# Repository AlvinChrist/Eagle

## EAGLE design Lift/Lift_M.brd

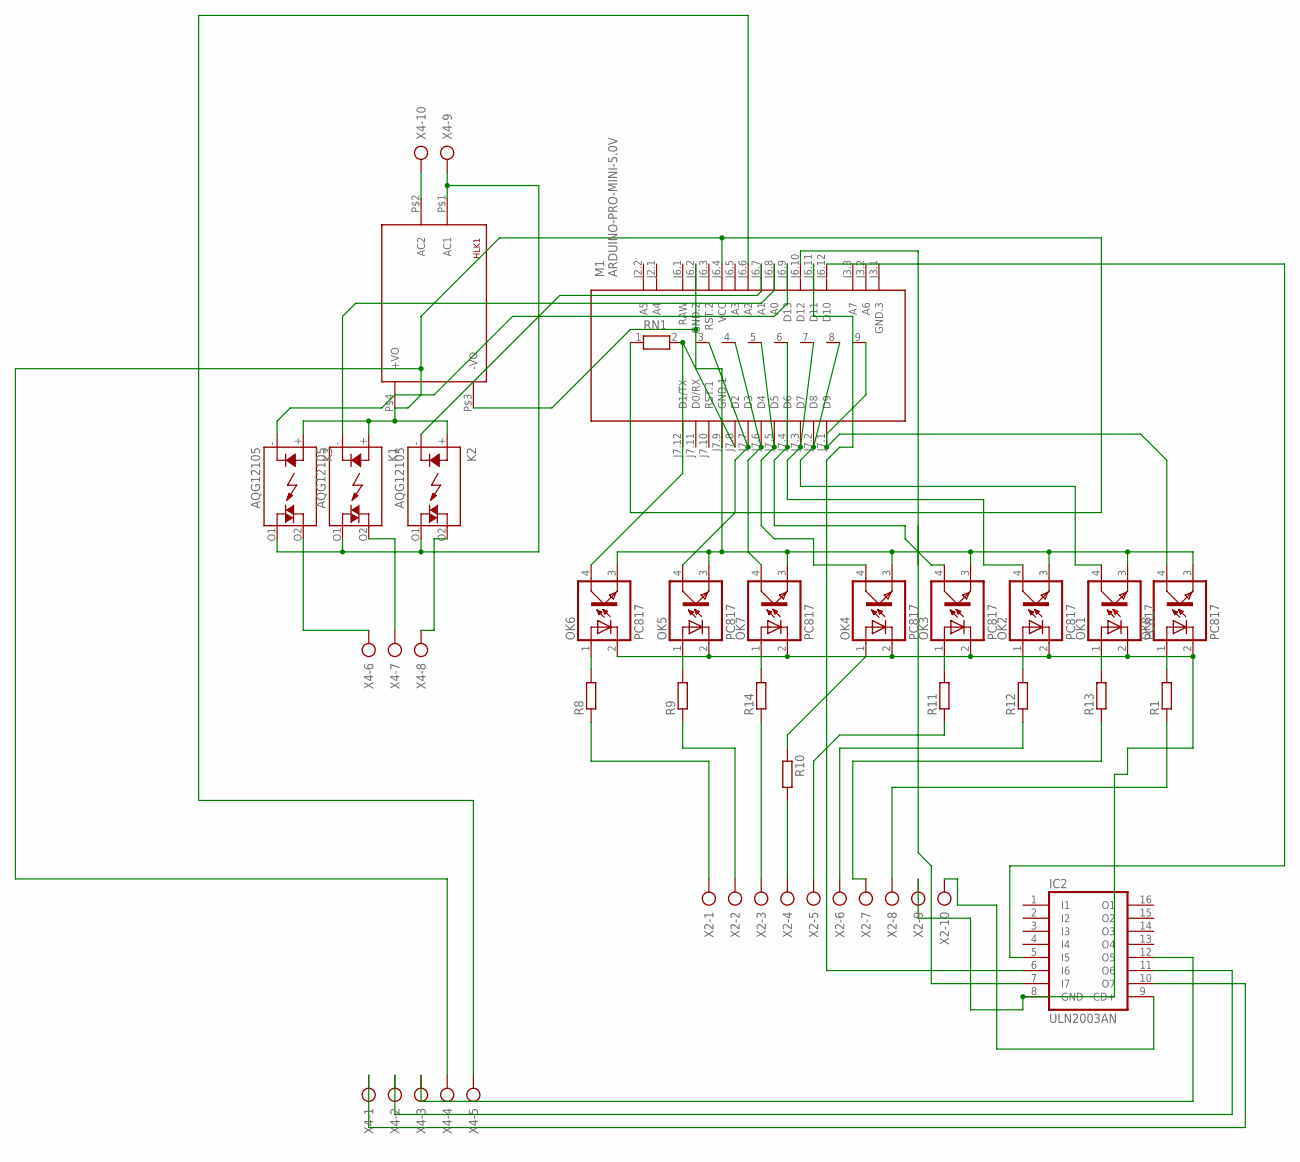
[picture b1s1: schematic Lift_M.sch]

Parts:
HLK1: HLK-PM013W; HLK-PM01
IC2: ULN2003AN; DIL16
K1, K2, K3: AQG12105; AQG
M1: ARDUINO-PRO-MINI-5.0V; ARDUINO-PRO-MINI
OK1, OK2, OK3, OK4, OK5, OK6, OK7, OK8: PC817; DIL04
R1, R8, R9, R10, R11, R12, R13, R14: R-EU_0204/7; 0204/7
RN1: RN08; RN-9
X2, X4: AK300/10

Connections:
5V: HLK1.P$4 (+VO), K1.+ (A), K2.+ (A), K3.+ (A), M1.J6.4 (VCC), RN1.1, X4.4
12V: IC2.9 (CD+), X2.10
GND1: HLK1.P$3 (-VO), M1.J6.2 (GND.2), M1.J7.9 (GND.1), OK1.3 (EMIT), OK2.3 (EMIT), OK3.3 (EMIT), OK4.3 (EMIT), OK5.3 (EMIT), OK6.3 (EMIT), OK7.3 (EMIT), OK8.3 (EMIT)
GND12V: IC2.8 (GND), OK1.2 (C), OK2.2 (C), OK3.2 (C), OK4.2 (C), OK5.2 (C), OK6.2 (C), OK7.2 (C), OK8.2 (C), X2.9
unnamed: OK2.1 (A), R12.2
unnamed: OK1.1 (A), R13.2
unnamed: OK3.1 (A), R11.2
unnamed: R10.2, X2.4
unnamed: OK7.1 (A), R14.2
unnamed: R14.1, X2.3
unnamed: R1.1, X2.8
unnamed: M1.J7.7 (D3), OK5.4 (COL), RN1.3
unnamed: M1.J7.5 (D5), OK4.4 (COL), RN1.5
unnamed: M1.J7.4 (D6), OK3.4 (COL), RN1.6
unnamed: IC2.10 (O7), X4.1
unnamed: M1.J7.6 (D4), OK7.4 (COL), RN1.4
unnamed: IC2.11 (O6), X4.2
unnamed: IC2.12 (O5), X4.3
unnamed: R8.1, X2.1
unnamed: R9.1, X2.2
unnamed: R11.1, X2.5
unnamed: M1.J7.3 (D7), OK2.4 (COL), RN1.7
unnamed: OK5.1 (A), R9.2
unnamed: R13.1, X2.7
unnamed: OK8.1 (A), R1.2
unnamed: HLK1.P$2 (AC2), X4.10
unnamed: R12.1, X2.6
unnamed: M1.J7.2 (D8), OK1.4 (COL), RN1.8
unnamed: IC2.5 (I5), M1.J6.12 (D10)
unnamed: HLK1.P$1 (AC1), K1.O1 (DS2), K2.O1 (DS2), K3.O1 (DS2), X4.9
unnamed: K3.O2 (DS1), X4.6
unnamed: K1.O2 (DS1), X4.7
unnamed: K2.O2 (DS1), X4.8
unnamed: M1.J7.1 (D9), OK8.4 (COL), RN1.9
unnamed: M1.J7.8 (D2), OK6.4 (COL), RN1.2
unnamed: OK6.1 (A), R8.2
unnamed: OK4.1 (A), R10.1
unnamed: IC2.7 (I7), M1.J6.10 (D12)
unnamed: IC2.6 (I6), M1.J6.11 (D11)
unnamed: M1.J6.6 (A2), X4.5
unnamed: K3.- (K), M1.J6.9 (D13)
unnamed: K1.- (K), M1.J6.8 (A0)
unnamed: K2.- (K), M1.J6.7 (A1)
RAW: M1.J6.1 (RAW)

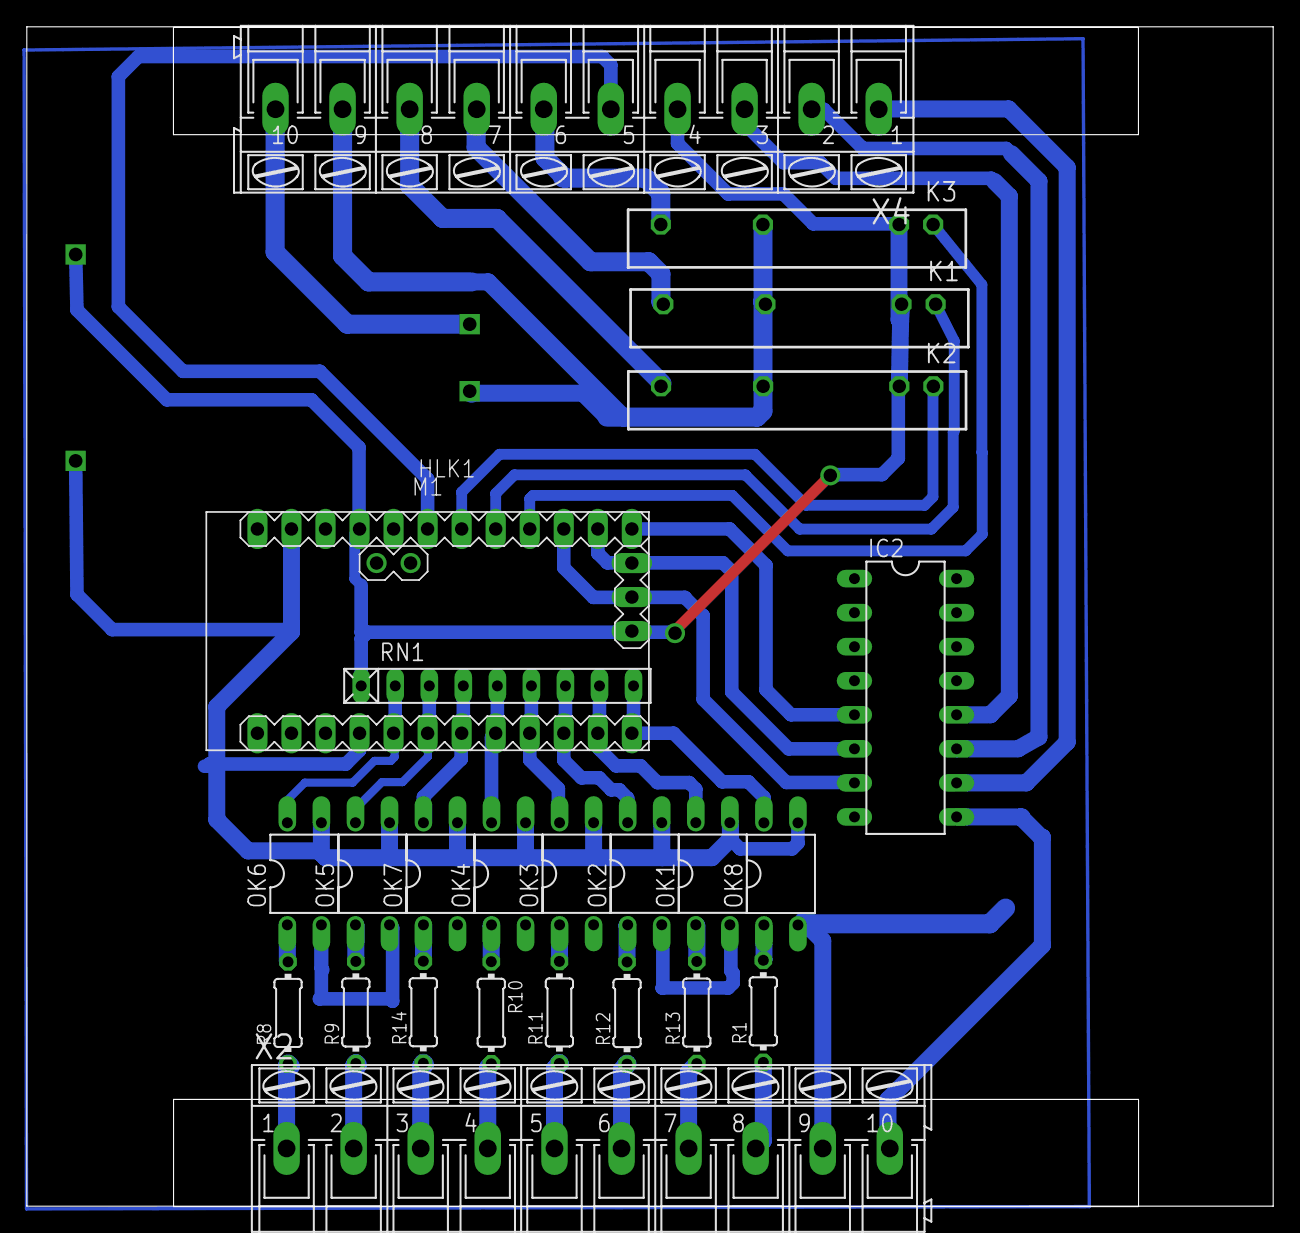
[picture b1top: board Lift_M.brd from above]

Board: 2 copper layers, 93.0 x 88.0 mm, 25 parts (0 on the bottom side), 43 nets.

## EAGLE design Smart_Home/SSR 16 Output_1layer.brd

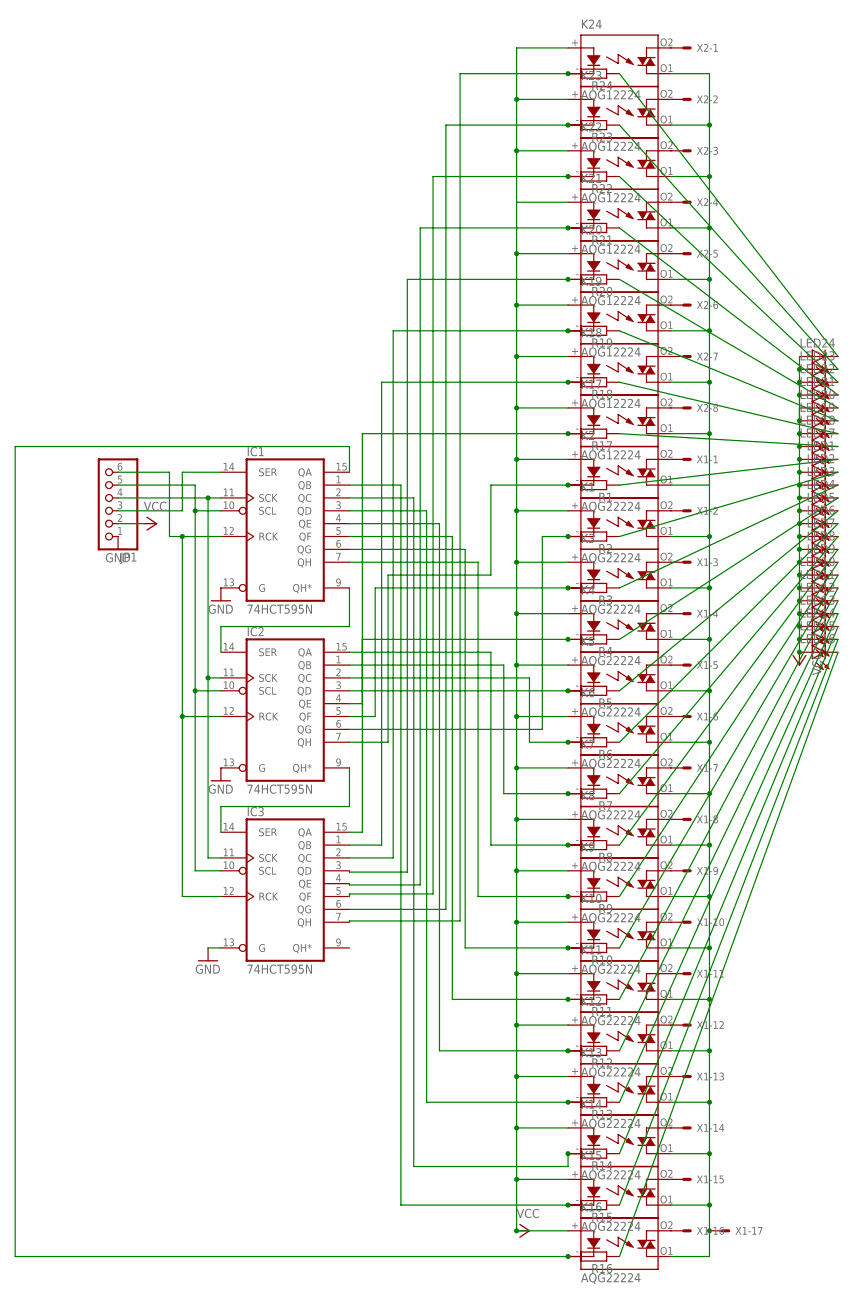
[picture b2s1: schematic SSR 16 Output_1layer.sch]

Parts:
IC1, IC2, IC3: 74HCT595N; DIL16
JP1: PINHD-1X6; 1X06
K1, K2, K3, K4, K5, K6, K7, K8, K9, K10, K11, K12, K13, K14, K15, K16: AQG22224; AQG
K17, K18, K19, K20, K21, K22, K23, K24: AQG12224; AQG
LED1, LED2, LED3, LED4, LED5, LED6, LED7, LED8, LED9, LED10, LED11, LED12, LED13, LED14, LED15, LED16, LED17, LED18, LED19, LED20, LED21, LED22, LED23, LED24: LED5MM
R1, R2, R3, R4, R5, R6, R7, R8, R9, R10, R11, R12, R13, R14, R15, R16, R17, R18, R19, R20, R21, R22, R23, R24: R0204/7; 0204/7
X1: KK-156-17
X2: KK-156-8

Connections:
GND: IC1.8 (GND), IC1.13 (G), IC2.8 (GND), IC2.13 (G), IC3.8 (GND), IC3.13 (G), JP1.1
unnamed: IC1.9 (QH*), IC2.14 (SER)
unnamed: IC1.11 (SCK), IC2.11 (SCK), IC3.11 (SCK), JP1.4
unnamed: IC1.10 (SCL), IC2.10 (SCL), IC3.10 (SCL), JP1.5
unnamed: IC1.12 (RCK), IC2.12 (RCK), IC3.12 (RCK), JP1.6
unnamed: LED1.K (C), R1.1
unnamed: IC1.15 (QA), K16.- (K), R16.2
unnamed: IC1.1 (QB), K15.- (K), R15.2
unnamed: IC1.2 (QC), K14.- (K), R14.2
unnamed: IC1.3 (QD), K13.- (K), R13.2
unnamed: IC1.4 (QE), K12.- (K), R12.2
unnamed: IC1.5 (QF), K11.- (K), R11.2
unnamed: IC1.6 (QG), K10.- (K), R10.2
unnamed: IC1.7 (QH), K9.- (K), R9.2
unnamed: IC2.15 (QA), K8.- (K), R8.2
unnamed: IC2.1 (QB), K7.- (K), R7.2
unnamed: IC2.2 (QC), K6.- (K), R6.2
unnamed: IC2.3 (QD), K5.- (K), R5.2
unnamed: IC2.4 (QE), K4.- (K), R4.2
unnamed: IC2.5 (QF), K3.- (K), R3.2
unnamed: IC2.6 (QG), K1.- (K), R2.2
unnamed: LED2.K (C), R2.1
unnamed: IC1.14 (SER), JP1.3
unnamed: K1.O1 (DS2), K2.O1 (DS2), K3.O1 (DS2), K4.O1 (DS2), K5.O1 (DS2), K6.O1 (DS2), K7.O1 (DS2), K8.O1 (DS2), K9.O1 (DS2), K10.O1 (DS2), K11.O1 (DS2), K12.O1 (DS2), K13.O1 (DS2), K14.O1 (DS2), K15.O1 (DS2), K16.O1 (DS2), K17.O1 (DS2), K18.O1 (DS2), K19.O1 (DS2), K20.O1 (DS2), K21.O1 (DS2), K22.O1 (DS2), K23.O1 (DS2), K24.O1 (DS2), X1.17
unnamed: K16.O2 (DS1), X1.16
unnamed: K15.O2 (DS1), X1.15
unnamed: K14.O2 (DS1), X1.14
unnamed: K13.O2 (DS1), X1.13
unnamed: K12.O2 (DS1), X1.12
unnamed: K11.O2 (DS1), X1.11
unnamed: K10.O2 (DS1), X1.10
unnamed: K9.O2 (DS1), X1.9
unnamed: K8.O2 (DS1), X1.8
unnamed: K7.O2 (DS1), X1.7
unnamed: K6.O2 (DS1), X1.6
unnamed: K5.O2 (DS1), X1.5
unnamed: K4.O2 (DS1), X1.4
unnamed: K3.O2 (DS1), X1.3
unnamed: K1.O2 (DS1), X1.2
unnamed: K2.O2 (DS1), X1.1
unnamed: IC2.7 (QH), K2.- (K), R1.2
unnamed: LED3.K (C), R3.1
unnamed: LED4.K (C), R4.1
unnamed: LED5.K (C), R5.1
unnamed: LED6.K (C), R6.1
unnamed: LED7.K (C), R7.1
unnamed: LED8.K (C), R8.1
unnamed: LED9.K (C), R9.1
unnamed: LED10.K (C), R10.1
unnamed: LED11.K (C), R11.1
unnamed: LED12.K (C), R12.1
unnamed: LED13.K (C), R13.1
unnamed: LED14.K (C), R14.1
unnamed: LED15.K (C), R15.1
unnamed: LED16.K (C), R16.1
unnamed: IC2.9 (QH*), IC3.14 (SER)
unnamed: IC3.15 (QA), K17.- (K), R17.2
unnamed: LED17.K (C), R17.1
unnamed: IC3.1 (QB), K18.- (K), R18.2
unnamed: LED18.K (C), R18.1
unnamed: IC3.2 (QC), K19.- (K), R19.2
unnamed: LED19.K (C), R19.1
unnamed: IC3.3 (QD), K20.- (K), R20.2
unnamed: LED20.K (C), R20.1
unnamed: IC3.4 (QE), K21.- (K), R21.2
unnamed: LED21.K (C), R21.1
unnamed: IC3.5 (QF), K22.- (K), R22.2
unnamed: LED22.K (C), R22.1
unnamed: K17.O2 (DS1), X2.8
unnamed: K18.O2 (DS1), X2.7
unnamed: K19.O2 (DS1), X2.6
unnamed: K20.O2 (DS1), X2.5
unnamed: K21.O2 (DS1), X2.4
unnamed: K22.O2 (DS1), X2.3
unnamed: K23.O2 (DS1), X2.2
unnamed: K24.O2 (DS1), X2.1
unnamed: IC3.6 (QG), K23.- (K), R23.2
unnamed: IC3.7 (QH), K24.- (K), R24.2
unnamed: LED23.K (C), R23.1
unnamed: LED24.K (C), R24.1
VCC: IC1.16 (VCC), IC2.16 (VCC), IC3.16 (VCC), JP1.2, K1.+ (A), K2.+ (A), K3.+ (A), K4.+ (A), K5.+ (A), K6.+ (A), K7.+ (A), K8.+ (A), K9.+ (A), K10.+ (A), K11.+ (A), K12.+ (A), K13.+ (A), K14.+ (A), K15.+ (A), K16.+ (A), K17.+ (A), K18.+ (A), K19.+ (A), K20.+ (A), K21.+ (A), K22.+ (A), K23.+ (A), K24.+ (A), LED1.A, LED2.A, LED3.A, LED4.A, LED5.A, LED6.A, LED7.A, LED8.A, LED9.A, LED10.A, LED11.A, LED12.A, LED13.A, LED14.A, LED15.A, LED16.A, LED17.A, LED18.A, LED19.A, LED20.A, LED21.A, LED22.A, LED23.A, LED24.A

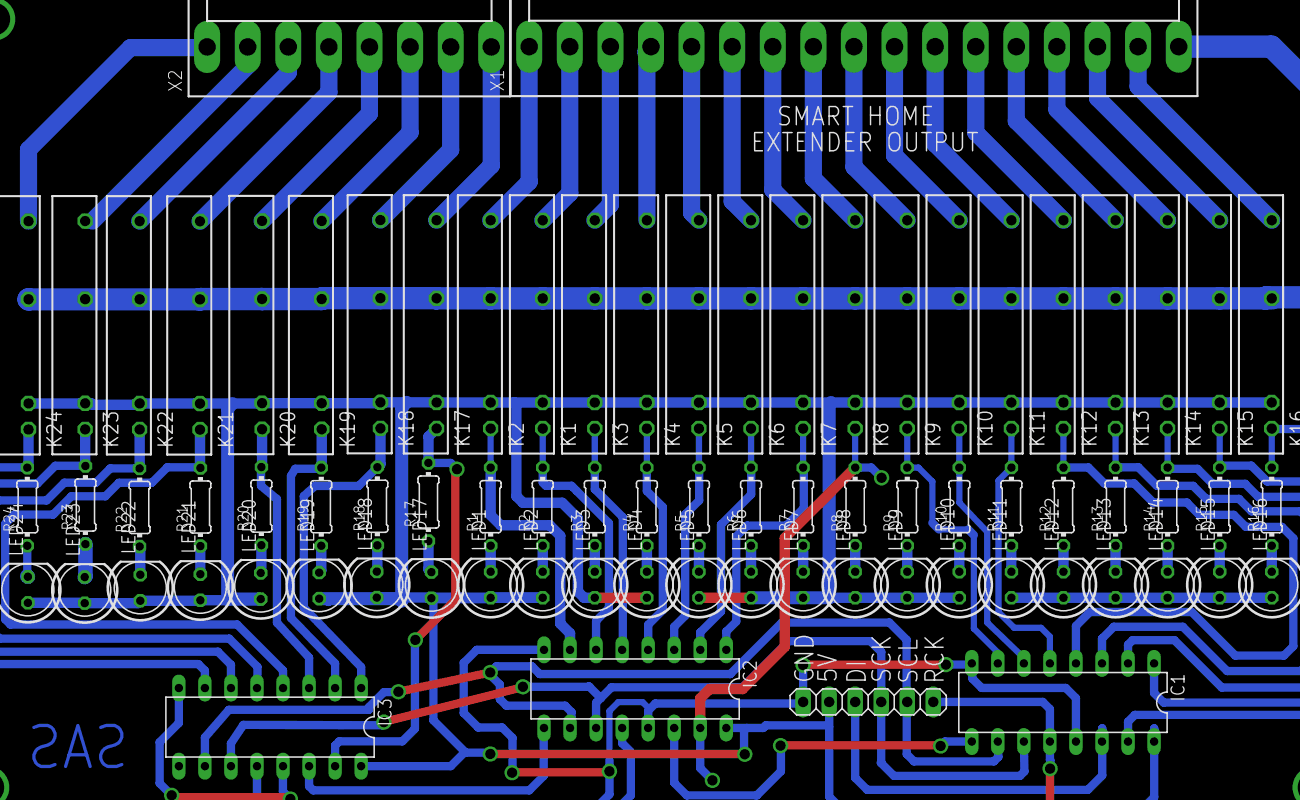
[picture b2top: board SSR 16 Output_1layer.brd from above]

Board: 2 copper layers, 78 parts (0 on the bottom side), 81 nets.

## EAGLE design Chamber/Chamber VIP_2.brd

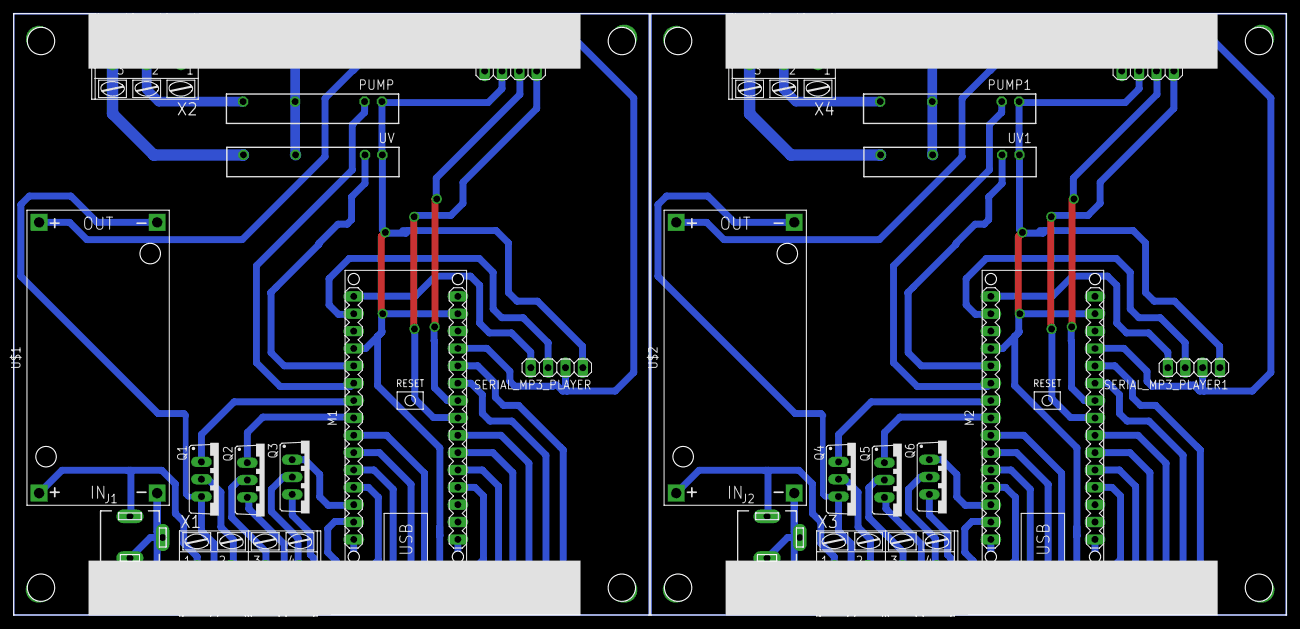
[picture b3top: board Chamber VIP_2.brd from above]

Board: 2 copper layers, 186.2 x 88.0 mm, 28 parts (0 on the bottom side), 62 nets.

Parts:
E$1, E$6: 1X12
E$2, E$3: 1X02
E$4, E$5: 1X04
J1, J2: DCJ0202
M1, M2: ARDUINO-NANO-3.0#ISP; ARDUINO-NANO-3.0
PUMP, PUMP1: AQG12105; AQG
Q1, Q2, Q3, Q4, Q5, Q6: IRF540; TO220BV
SERIAL_MP3_PLAYER, SERIAL_MP3_PLAYER1: 1X04
U$1, U$2: DC-DC-STEP-DOWN-LM2596
UV, UV1: AQG12105; AQG
X1, X3: AK300/4
X2, X4: AK300/3

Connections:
+5V: E$4.1, M1.J2.4, SERIAL_MP3_PLAYER.2, U$1.OUT+
+5V1: E$5.1, M2.J2.4, SERIAL_MP3_PLAYER1.2, U$2.OUT+
GND: E$1.7, E$4.2, J1.2, J1.3, M1.J1.4, M1.J2.2, PUMP.-, Q1.S, Q2.S, Q3.S, SERIAL_MP3_PLAYER.1, U$1.IN-, U$1.OUT-, UV.-
GND1: E$5.2, E$6.7, J2.2, J2.3, M2.J1.4, M2.J2.2, PUMP1.-, Q4.S, Q5.S, Q6.S, SERIAL_MP3_PLAYER1.1, U$2.IN-, U$2.OUT-, UV1.-
unnamed: Q3.D, X1.4
unnamed: J1.1, U$1.IN+, X1.1
unnamed: Q1.D, X1.2
unnamed: Q2.D, X1.3
unnamed: J2.1, U$2.IN+, X3.1
unnamed: PUMP.O2, X2.2
unnamed: PUMP.O1, UV.O1, X2.1
unnamed: Q4.D, X3.2
unnamed: PUMP1.O2, X4.2
unnamed: PUMP1.O1, UV1.O1, X4.1
unnamed: M2.J1.5, UV1.+
unnamed: Q6.D, X3.4
unnamed: M1.J1.5, UV.+
unnamed: Q5.D, X3.3
unnamed: M2.J1.6, PUMP1.+
unnamed: M1.J1.6, PUMP.+
unnamed: E$1.2, M1.J1.15
unnamed: UV.O2, X2.3
unnamed: E$6.2, M2.J1.15
unnamed: UV1.O2, X4.3
S$1: E$4.3, M1.J2.7
S$4: M1.J1.2, SERIAL_MP3_PLAYER.3
S$5: M1.J1.1, SERIAL_MP3_PLAYER.4
S$6: E$1.6, M1.J1.9
S$7: M1.J1.7, Q1.G
S$8: E$1.4, M1.J1.11
S$9: E$1.3, M1.J1.12
S$10: M1.J1.13, Q3.G
S$11: E$1.1, M1.J1.14
S$12: E$2.2, M1.J2.5
S$13: E$2.1, M1.J2.6
S$14: E$1.12, M1.J2.9
S$15: E$1.11, M1.J2.10
S$16: E$1.10, M1.J2.11
S$17: E$1.9, M1.J2.12
S$18: E$1.8, M1.J2.15
S$19: M1.J1.8, Q2.G
S$20: E$4.4, M1.J2.8
S$21: E$1.5, M1.J1.10
S$23: E$6.5, M2.J1.10
S$24: E$6.4, M2.J1.11
S$25: E$6.6, M2.J1.9
S$26: M2.J1.2, SERIAL_MP3_PLAYER1.3
S$27: M2.J1.7, Q4.G
S$29: M2.J1.1, SERIAL_MP3_PLAYER1.4
S$30: E$6.3, M2.J1.12
S$31: M2.J1.13, Q6.G
S$32: E$6.1, M2.J1.14
S$33: E$3.2, M2.J2.5
S$34: E$3.1, M2.J2.6
S$35: E$6.12, M2.J2.9
S$36: E$6.11, M2.J2.10
S$37: E$6.10, M2.J2.11
S$38: E$6.9, M2.J2.12
S$39: E$6.8, M2.J2.15
S$40: E$5.3, M2.J2.7
S$41: E$5.4, M2.J2.8
S$42: M2.J1.8, Q5.G

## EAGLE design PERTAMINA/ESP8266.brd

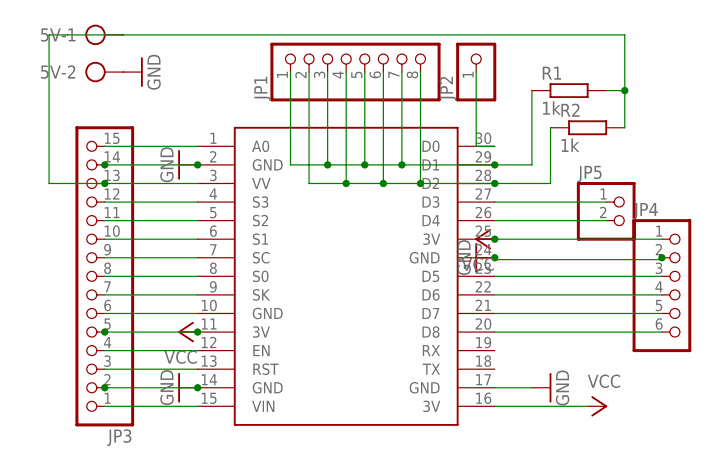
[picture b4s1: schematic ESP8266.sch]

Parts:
5V: AK300/2
JP1: PINHD-1X8; 1X08
JP2: PINHD-1X1; 1X01
JP3: PINHD-1X15; 1X15
JP4: PINHD-1X6; 1X06
JP5: PINHD-1X2; 1X02
R1, R2: 1k; 0204/7
U$1: NODEMCU

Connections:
GND: 5V.2, JP3.2, JP3.14, JP4.2, U$1.2 (GND), U$1.14 (GND), U$1.17 (GND), U$1.24 (GND)
unnamed: JP3.1, U$1.15 (VIN)
unnamed: JP3.3, U$1.13 (RST)
unnamed: JP3.4, U$1.12 (EN)
unnamed: JP3.6, U$1.10 (GND)
unnamed: JP3.7, U$1.9 (SK)
unnamed: JP3.8, U$1.8 (S0)
unnamed: JP3.9, U$1.7 (SC)
unnamed: JP3.10, U$1.6 (S1)
unnamed: JP3.11, U$1.5 (S2)
unnamed: JP3.12, U$1.4 (S3)
unnamed: 5V.1, JP3.13, R1.2, R2.2, U$1.3 (VV)
unnamed: JP3.15, U$1.1 (A0)
unnamed: JP4.3, U$1.23 (D5)
unnamed: JP4.4, U$1.22 (D6)
unnamed: JP4.5, U$1.21 (D7)
unnamed: JP4.6, U$1.20 (D8)
unnamed: JP5.1, U$1.27 (D3)
unnamed: JP5.2, U$1.26 (D4)
SCL: JP1.1, JP1.3, JP1.5, JP1.7, R1.1, U$1.29 (D1)
SDA: JP1.2, JP1.4, JP1.6, JP1.8, R2.1, U$1.28 (D2)
VCC: JP3.5, JP4.1, U$1.11 (3V), U$1.16 (3V), U$1.25 (3V)

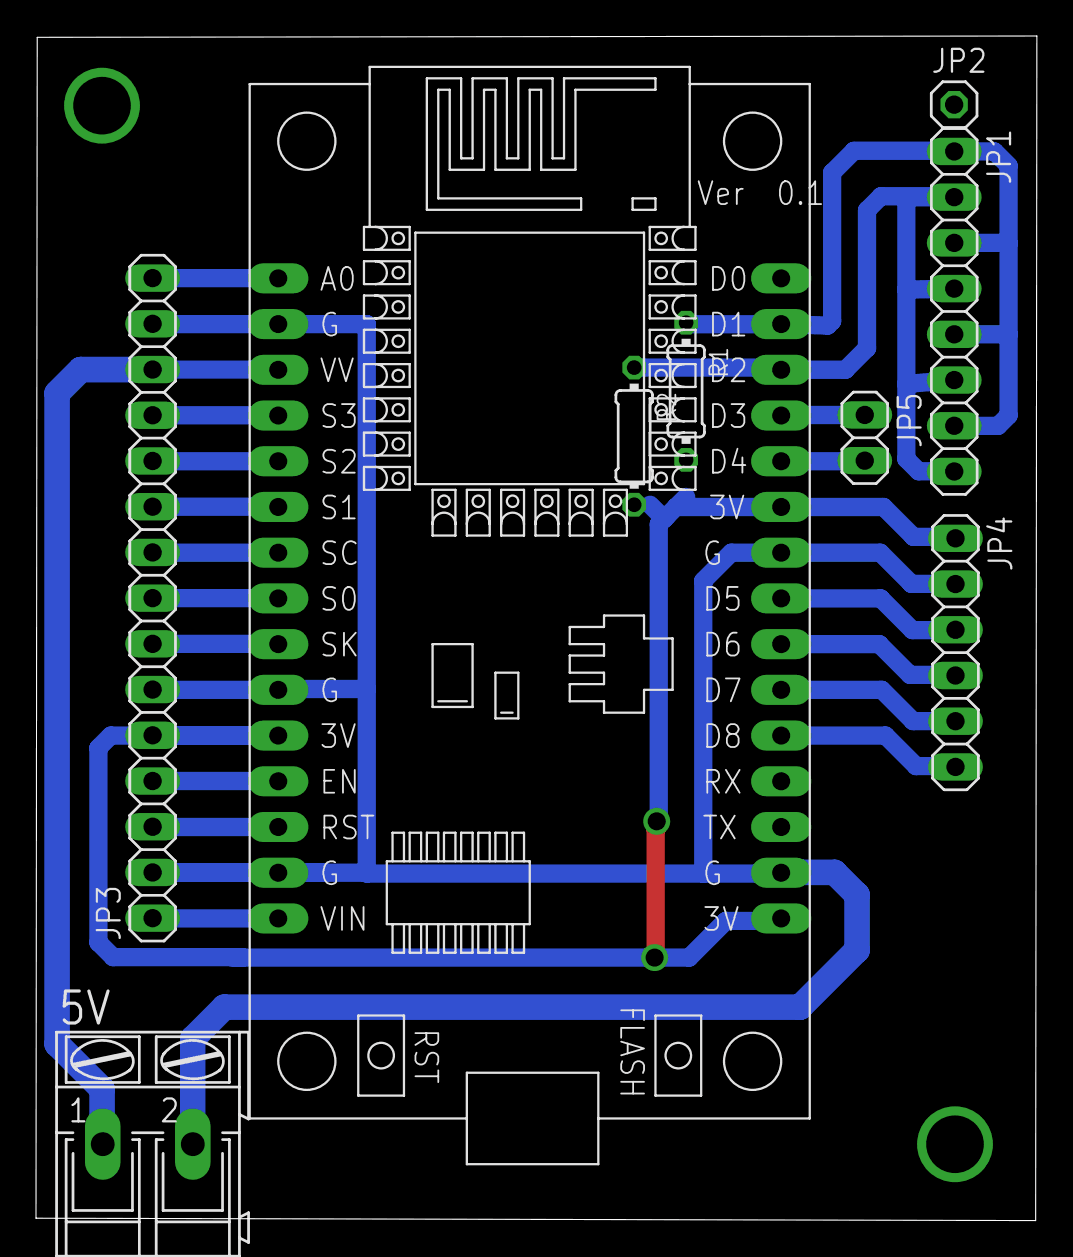
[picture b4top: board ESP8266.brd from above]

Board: 2 copper layers, 55.6 x 65.8 mm, 9 parts (0 on the bottom side), 22 nets.

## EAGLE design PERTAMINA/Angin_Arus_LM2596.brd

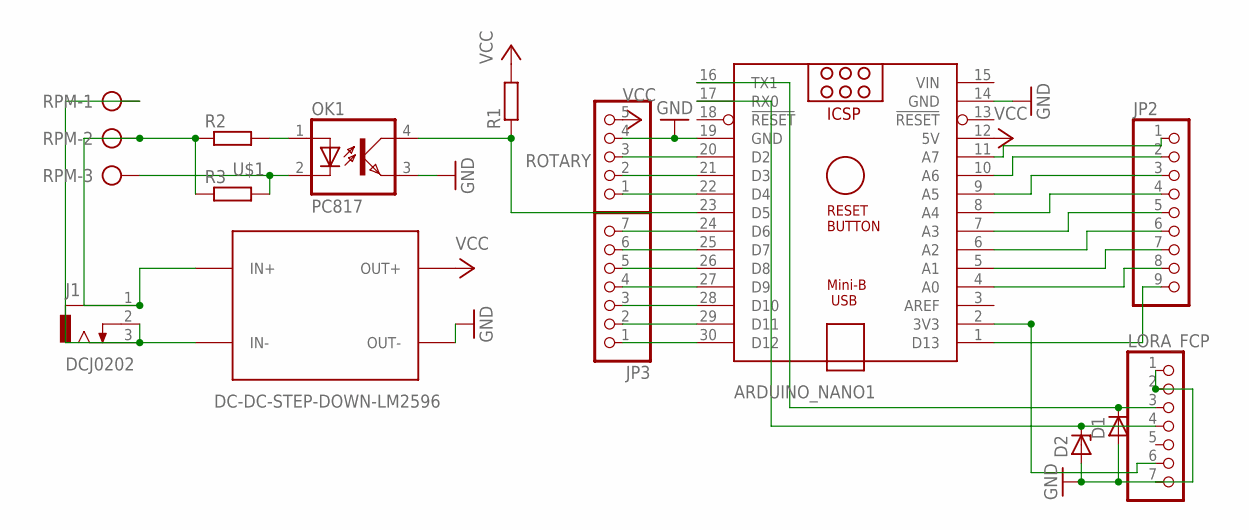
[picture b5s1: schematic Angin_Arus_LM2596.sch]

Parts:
ARDUINO_NANO1: ARDUINO_NANO
D1, D2: ZENER-DIODEDO35Z10; DO35Z10
J1: DCJ0202
JP2: PINHD-1X9; 1X09
JP3: PINHD-1X7; 1X07
LORA_FCP: PINHD-1X7; 1X07
OK1: PC817; DIL04
R1, R2, R3: R-EU_0204/7; 0204/7
ROTARY: PINHD-1X5; 1X05
RPM: AK300/3
U$1: DC-DC-STEP-DOWN-LM2596

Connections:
3.3V: ARDUINO_NANO1.2 (3V3), LORA_FCP.6
12V: J1.1, R2.1, R3.1, RPM.2, U$1.IN+
GND: ARDUINO_NANO1.14 (GND), ARDUINO_NANO1.19 (GND), D1.A, D2.A, LORA_FCP.1, LORA_FCP.2, LORA_FCP.7, OK1.3 (EMIT), ROTARY.4, U$1.OUT-
GND12V: J1.2, J1.3, RPM.1, U$1.IN-
unnamed: ARDUINO_NANO1.23 (D5), OK1.4 (COL), R1.1
unnamed: OK1.1 (A), R2.2
unnamed: ARDUINO_NANO1.20 (D2), ROTARY.3
unnamed: ARDUINO_NANO1.21 (D3), ROTARY.2
unnamed: ARDUINO_NANO1.22 (D4), ROTARY.1
unnamed: ARDUINO_NANO1.8 (A4), JP2.4
unnamed: ARDUINO_NANO1.1 (D13), JP2.9
unnamed: ARDUINO_NANO1.4 (A0), JP2.8
unnamed: ARDUINO_NANO1.5 (A1), JP2.7
unnamed: ARDUINO_NANO1.6 (A2), JP2.6
unnamed: ARDUINO_NANO1.7 (A3), JP2.5
unnamed: ARDUINO_NANO1.9 (A5), JP2.3
unnamed: ARDUINO_NANO1.10 (A6), JP2.2
unnamed: ARDUINO_NANO1.11 (A7), JP2.1
unnamed: ARDUINO_NANO1.30 (D12), JP3.1
unnamed: ARDUINO_NANO1.29 (D11), JP3.2
unnamed: ARDUINO_NANO1.28 (D10), JP3.3
unnamed: ARDUINO_NANO1.27 (D9), JP3.4
unnamed: ARDUINO_NANO1.26 (D8), JP3.5
unnamed: ARDUINO_NANO1.25 (D7), JP3.6
unnamed: ARDUINO_NANO1.24 (D6), JP3.7
RX: ARDUINO_NANO1.16 (TX1), D1.C, LORA_FCP.3
SIGNAL: OK1.2 (C), R3.2, RPM.3
TX: ARDUINO_NANO1.17 (RX0), D2.C, LORA_FCP.4
VCC: ARDUINO_NANO1.12 (5V), R1.2, ROTARY.5, U$1.OUT+
VIN: ARDUINO_NANO1.15 (VIN)

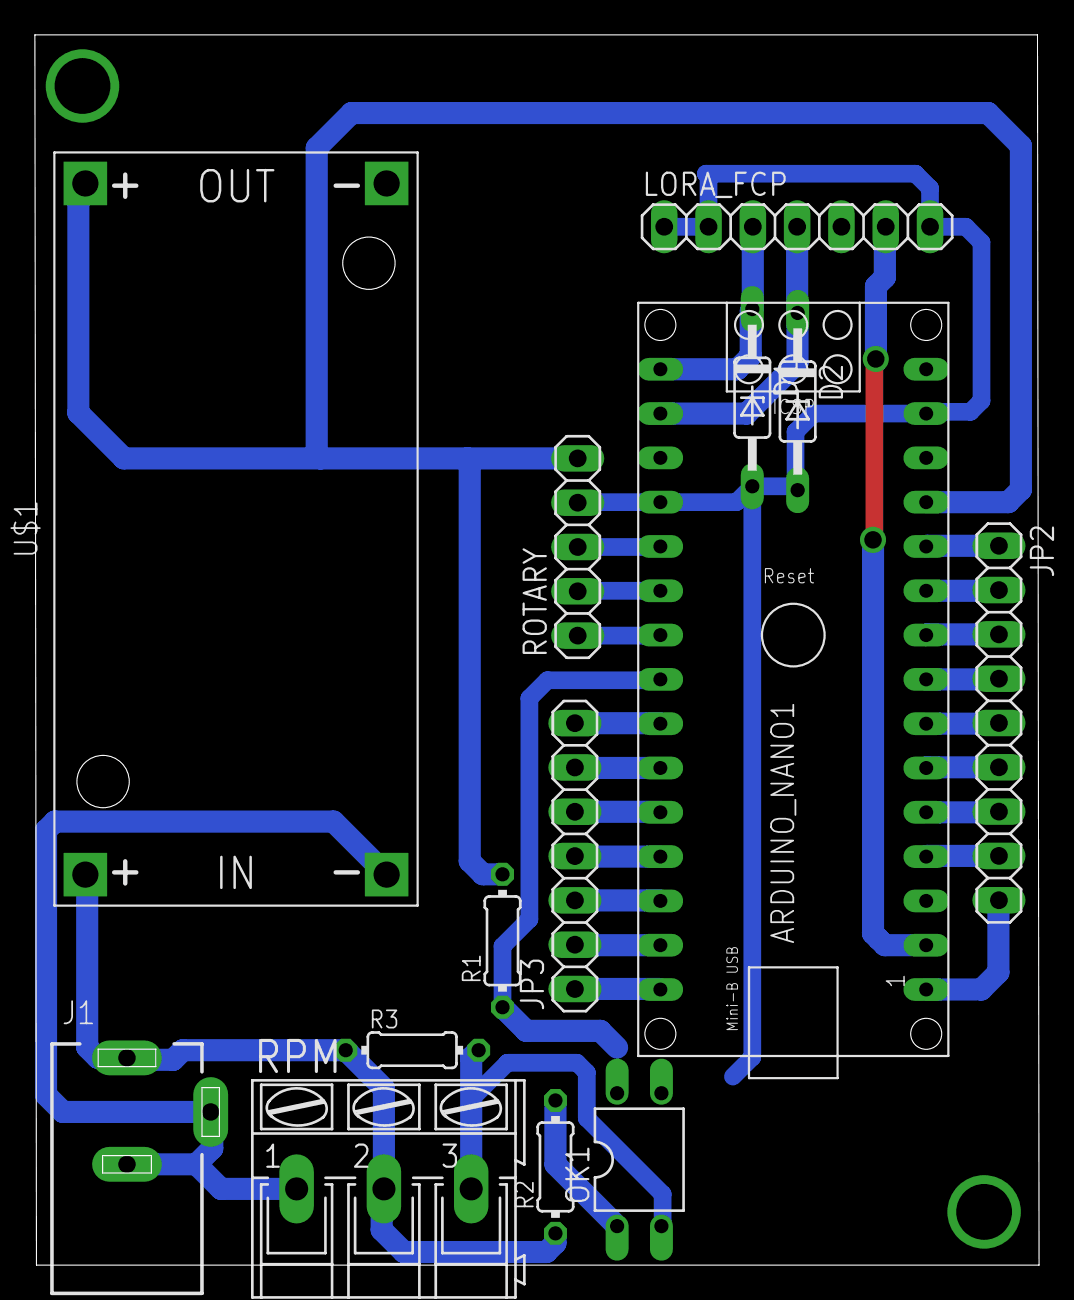
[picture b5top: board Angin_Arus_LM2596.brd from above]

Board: 2 copper layers, 57.6 x 70.5 mm, 14 parts (0 on the bottom side), 29 nets.

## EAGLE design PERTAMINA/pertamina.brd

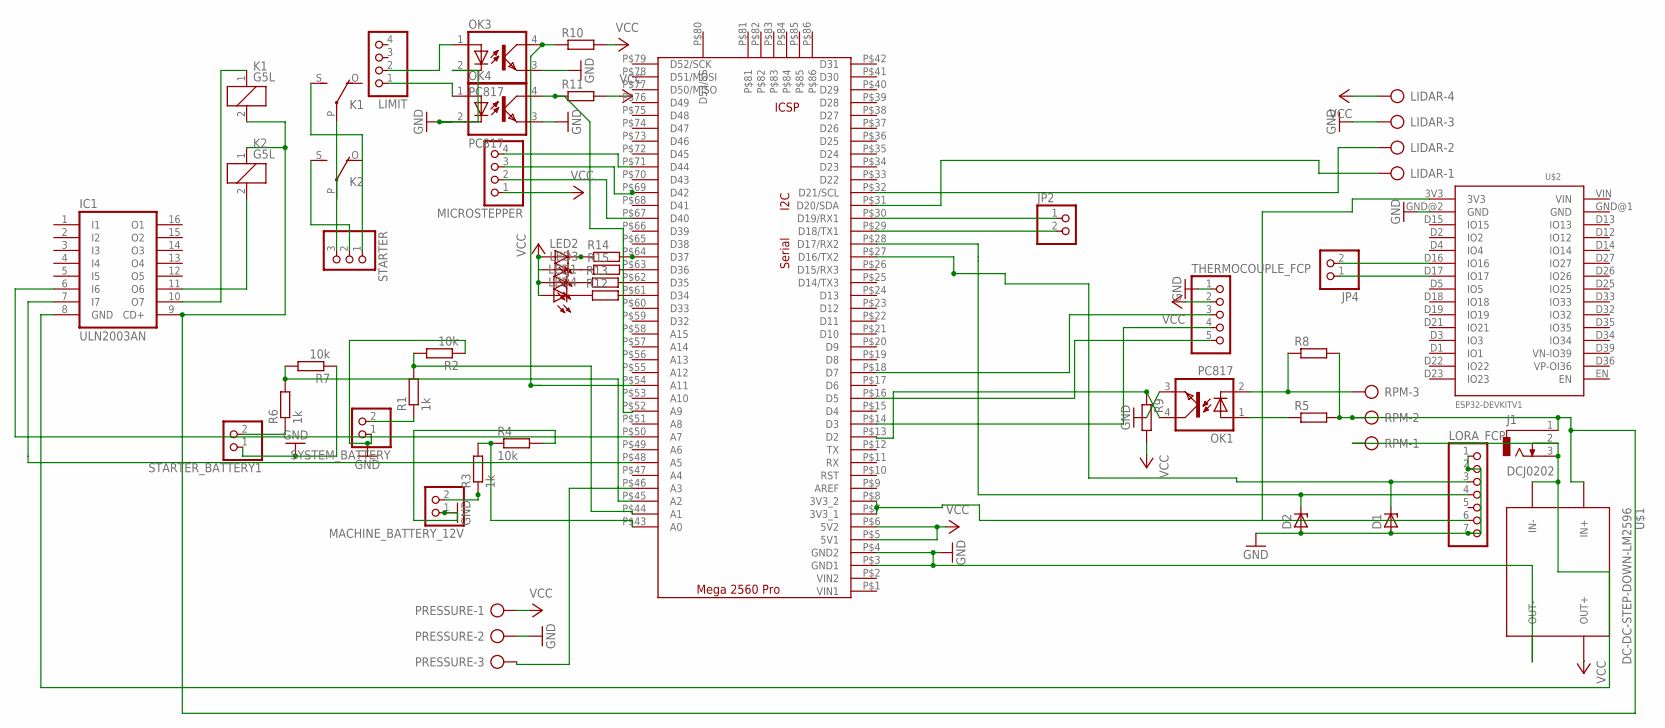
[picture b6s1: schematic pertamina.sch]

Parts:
D1, D2: ZENER-DIODEDO35Z10; DO35Z10
IC1: ULN2003AN; DIL16
J1: DCJ0202
JP2, JP4: PINHD-1X2; 1X02
K1, K2: G5L; G5LE
LED1, LED2, LED3, LED4: LED5MM
LIDAR: AK300/4
LIMIT: PINHD-1X4; 1X04
LORA_FCP: PINHD-1X7; 1X07
MACHINE_BATTERY_12V: PINHD-1X2; 1X02
MICROSTEPPER: PINHD-1X4; 1X04
OK1, OK3, OK4: PC817; DIL04
PRESSURE: AK300/3
R1, R3, R6: 1k; 0204/7
R2, R4, R7: 10k; 0204/7
R5, R8, R9, R10, R11, R12, R13, R14, R15: R-EU_0204/7; 0204/7
RPM: AK300/3
STARTER: PINHD-1X3; 1X03
STARTER_BATTERY1: PINHD-1X2; 1X02
SYSTEM_BATTERY: PINHD-1X2; 1X02
THERMOCOUPLE_FCP: PINHD-1X5; 1X05
U$1: DC-DC-STEP-DOWN-LM2596
U$2: ESP32DEVKITV1; ESP32-DEVKITV1
U$3: MEGAPROMINI

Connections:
3.3V: LORA_FCP.6, U$2.3V3, U$3.P$7 (3V3_1), U$3.P$8 (3V3_2)
5V: R1.2, R2.2, U$3.P$44 (A1)
5V1: R6.2, R7.2, U$3.P$45 (A2)
5V_ARDU: LED1.A, LED2.A, LED3.A, LED4.A, LIDAR.4, MICROSTEPPER.1, PRESSURE.1, R9.2, R10.2, R11.2, THERMOCOUPLE_FCP.2, U$1.OUT+, U$3.P$5 (5V1), U$3.P$6 (5V2)
GND: D1.A, D2.A, LIDAR.3, LORA_FCP.1, LORA_FCP.2, LORA_FCP.7, MACHINE_BATTERY_12V.1, OK1.3 (EMIT), OK3.2 (C), OK3.3 (EMIT), OK4.2 (C), OK4.3 (EMIT), PRESSURE.2, R2.1, R4.2, R7.1, STARTER_BATTERY1.1, SYSTEM_BATTERY.1, THERMOCOUPLE_FCP.1, U$1.OUT-, U$2.GND@2 (GND), U$3.P$3 (GND1), U$3.P$4 (GND2)
unnamed: JP2.1, U$3.P$30 (D19/RX1)
unnamed: JP2.2, U$3.P$29 (D18/TX1)
unnamed: R3.2, R4.1, U$3.P$43 (A0)
unnamed: IC1.10 (O7), K1.1
unnamed: THERMOCOUPLE_FCP.5, U$3.P$16 (D5)
unnamed: THERMOCOUPLE_FCP.4, U$3.P$14 (D3)
unnamed: THERMOCOUPLE_FCP.3, U$3.P$18 (D7)
unnamed: D2.C, LORA_FCP.4, U$3.P$28 (D17/RX2)
unnamed: R1.1, SYSTEM_BATTERY.2
unnamed: IC1.9 (CD+), J1.1, K1.2, K2.1, R5.2, R8.2, RPM.2, U$1.IN+
unnamed: D1.C, LORA_FCP.3, U$3.P$27 (D16/TX2)
unnamed: MACHINE_BATTERY_12V.2, R3.1
unnamed: IC1.8 (GND), J1.2, J1.3, RPM.1, U$1.IN-
unnamed: OK1.1 (A), R5.1
unnamed: OK1.4 (COL), R9.1, U$3.P$13 (D2)
unnamed: OK1.2 (C), R8.1, RPM.3
unnamed: JP4.1, U$2.D17 (IO17)
unnamed: JP4.2, U$2.D16 (IO16)
unnamed: IC1.7 (I7), U$3.P$48 (A5)
unnamed: R6.1, STARTER_BATTERY1.2
unnamed: R12.2, U$3.P$61 (D34)
unnamed: LED4.K (C), R12.1
unnamed: R14.2, U$3.P$64 (D37)
unnamed: IC1.6 (I6), U$3.P$50 (A7)
unnamed: MICROSTEPPER.4, U$3.P$71 (D44)
unnamed: MICROSTEPPER.2, U$3.P$67 (D40)
unnamed: MICROSTEPPER.3, U$3.P$69 (D42)
unnamed: PRESSURE.3, U$3.P$46 (A3)
unnamed: LED2.K (C), R14.1
unnamed: IC1.11 (O6), K2.2
unnamed: R13.2, U$3.P$62 (D35)
unnamed: LED1.K (C), R13.1
unnamed: R15.2, U$3.P$63 (D36)
unnamed: LED3.K (C), R15.1
unnamed: LIMIT.1, OK4.1 (A)
unnamed: LIMIT.2, OK3.1 (A)
unnamed: OK4.4 (COL), R11.1, U$3.P$52 (A9)
unnamed: K1.P, K2.P, STARTER.3
unnamed: K2.S, STARTER.2
unnamed: K1.S, STARTER.1
unnamed: OK3.4 (COL), R10.1, U$3.P$54 (A11)
SCL: LIDAR.2, U$3.P$32 (D21/SCL)
SDA: LIDAR.1, U$3.P$31 (D20/SDA)

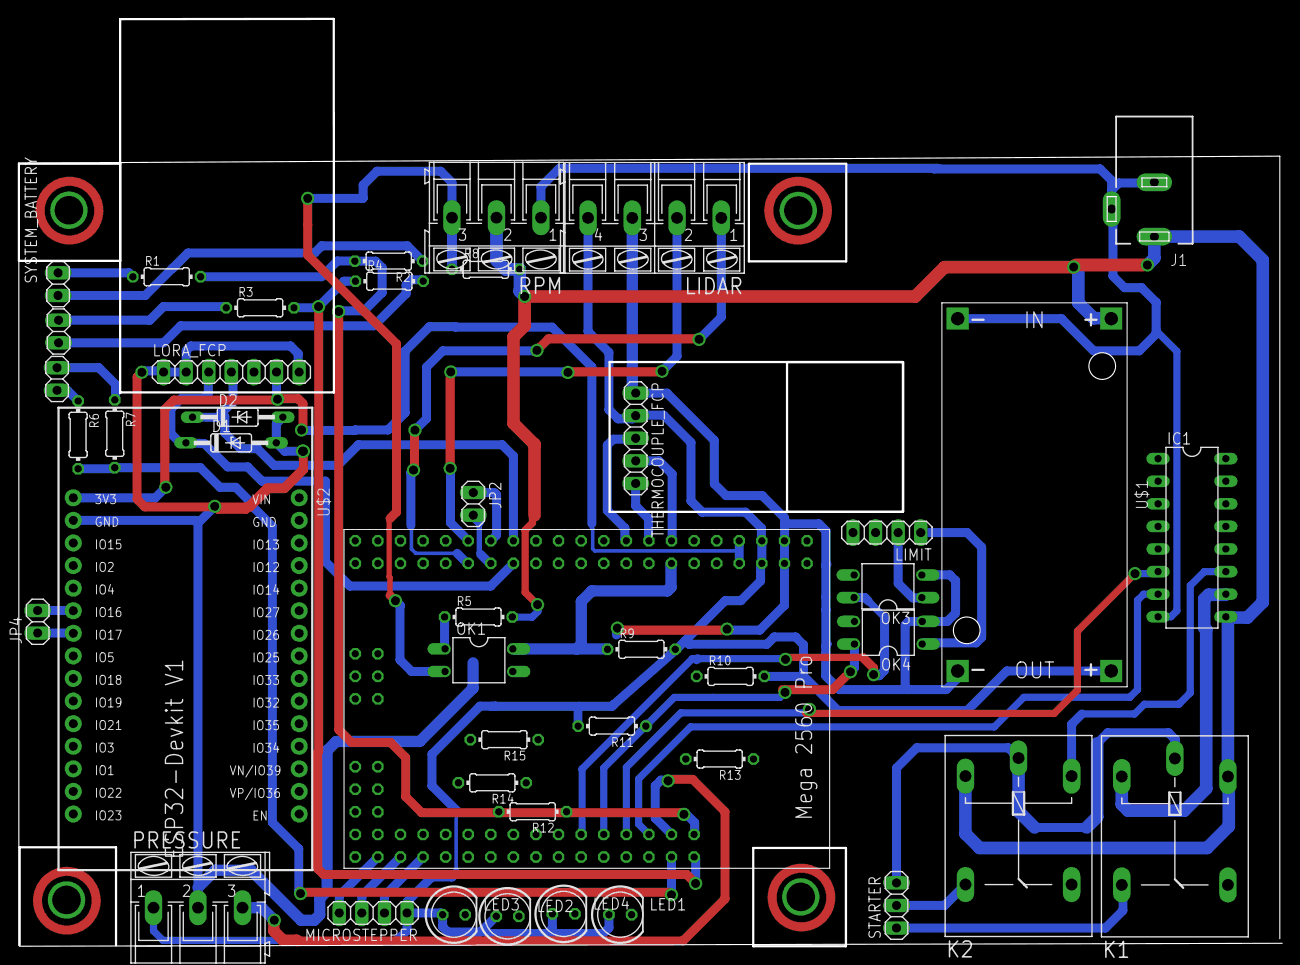
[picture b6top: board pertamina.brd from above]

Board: 2 copper layers, 141.9 x 104.3 mm, 44 parts (0 on the bottom side), 48 nets.

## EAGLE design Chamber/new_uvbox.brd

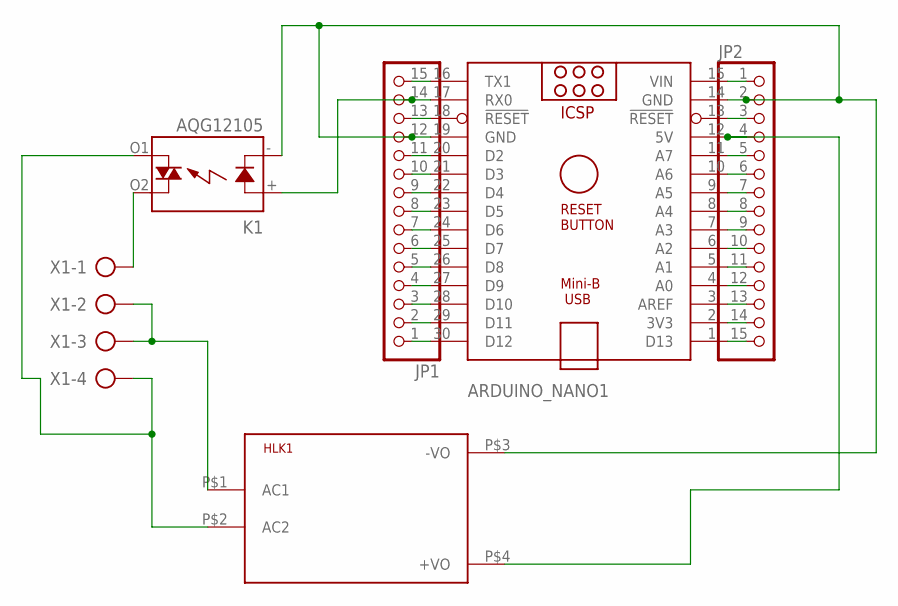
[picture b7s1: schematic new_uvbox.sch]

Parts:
ARDUINO_NANO1: ARDUINO_NANO
HLK1: HLK-PM013W; HLK-PM01
JP1, JP2: PINHD-1X15; 1X15
K1: AQG12105; AQG
X1: AK300/4

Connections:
unnamed: ARDUINO_NANO1.16 (TX1), JP1.15
unnamed: ARDUINO_NANO1.17 (RX0), JP1.14, K1.+ (A)
unnamed: ARDUINO_NANO1.18 (!RESET), JP1.13
unnamed: ARDUINO_NANO1.14 (GND), ARDUINO_NANO1.19 (GND), HLK1.P$3 (-VO), JP1.12, JP2.2, K1.- (K)
unnamed: ARDUINO_NANO1.30 (D12), JP1.1
unnamed: ARDUINO_NANO1.29 (D11), JP1.2
unnamed: ARDUINO_NANO1.28 (D10), JP1.3
unnamed: ARDUINO_NANO1.27 (D9), JP1.4
unnamed: ARDUINO_NANO1.26 (D8), JP1.5
unnamed: ARDUINO_NANO1.25 (D7), JP1.6
unnamed: ARDUINO_NANO1.24 (D6), JP1.7
unnamed: ARDUINO_NANO1.23 (D5), JP1.8
unnamed: ARDUINO_NANO1.22 (D4), JP1.9
unnamed: ARDUINO_NANO1.21 (D3), JP1.10
unnamed: ARDUINO_NANO1.20 (D2), JP1.11
unnamed: ARDUINO_NANO1.15 (VIN), JP2.1
unnamed: HLK1.P$2 (AC2), K1.O1 (DS2), X1.4
unnamed: ARDUINO_NANO1.13 (!RESET), JP2.3
unnamed: ARDUINO_NANO1.12 (5V), HLK1.P$4 (+VO), JP2.4
unnamed: ARDUINO_NANO1.11 (A7), JP2.5
unnamed: ARDUINO_NANO1.10 (A6), JP2.6
unnamed: ARDUINO_NANO1.9 (A5), JP2.7
unnamed: ARDUINO_NANO1.8 (A4), JP2.8
unnamed: ARDUINO_NANO1.7 (A3), JP2.9
unnamed: ARDUINO_NANO1.6 (A2), JP2.10
unnamed: ARDUINO_NANO1.5 (A1), JP2.11
unnamed: ARDUINO_NANO1.4 (A0), JP2.12
unnamed: ARDUINO_NANO1.3 (AREF), JP2.13
unnamed: ARDUINO_NANO1.2 (3V3), JP2.14
unnamed: ARDUINO_NANO1.1 (D13), JP2.15
unnamed: HLK1.P$1 (AC1), X1.2, X1.3
unnamed: K1.O2 (DS1), X1.1

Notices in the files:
parts and their libraries:
diy-modules: Released under the Creative Commons Attribution 4.0 International License: http://creativecommons.org/licenses/by/4.0
